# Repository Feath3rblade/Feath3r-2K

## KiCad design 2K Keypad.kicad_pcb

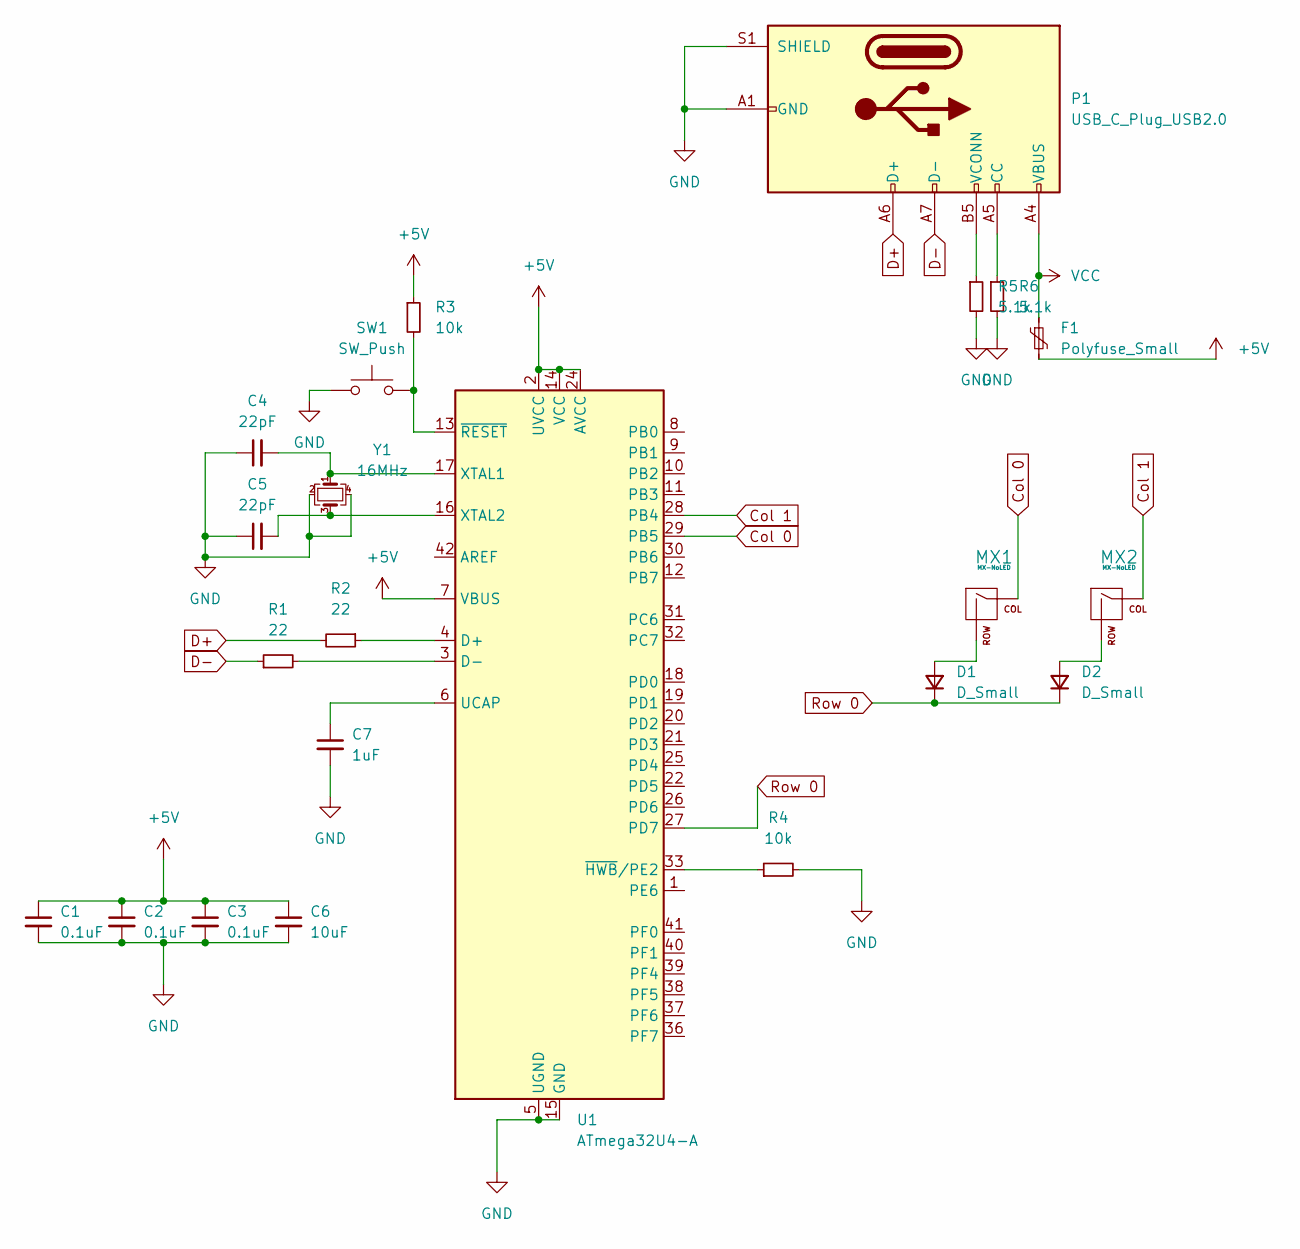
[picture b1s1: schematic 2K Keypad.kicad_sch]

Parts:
C1, C2, C3: 0.1uF; C_0805_2012Metric
C4, C5: 22pF; C_0805_2012Metric
C6: 10uF; C_0805_2012Metric
C7: 1uF; C_0805_2012Metric
D1, D2: D_Small; D_SOD-123
F1: Polyfuse_Small; Fuse_1206_3216Metric
MX1, MX2: MX-NoLED; MXOnly-1U-NoLED
P1: USB_C_Plug_USB2.0; USB_C_Receptacle_GCT_USB4085
R1, R2: 22; R_0805_2012Metric
R3, R4: 10k; R_0805_2012Metric
R5, R6: 5.1k; R_0805_2012Metric
SW1: SW_Push; SKQG-1155865
U1: ATmega32U4-A; TQFP-44_10x10mm_P0.8mm
Y1: 16MHz; Crystal_SMD_3225-4Pin_3.2x2.5mm

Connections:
+5V: C1.1, C2.1, C3.1, C6.1, F1.2, R3.1, U1.2 (UVCC), U1.7 (VBUS), U1.14 (VCC), U1.24 (AVCC), U1.34 (VCC), U1.44 (AVCC)
Col 0: MX1.1 (COL), U1.29 (PB5)
Col 1: MX2.1 (COL), U1.28 (PB4)
D+: P1.A6 (D+), R2.2
D-: P1.A7 (D-), R1.1
GND: C1.2, C2.2, C3.2, C4.1, C5.1, C6.2, C7.2, P1.A1 (GND), P1.A12 (GND), P1.B1 (GND), P1.B12 (GND), P1.S1 (SHIELD), R4.2, R5.2, R6.2, SW1.1, U1.5 (UGND), U1.15 (GND), U1.23 (GND), U1.35 (GND), U1.43 (GND), Y1.2, Y1.4
unnamed: C4.2, U1.17 (XTAL1), Y1.1
unnamed: C5.2, U1.16 (XTAL2), Y1.3
unnamed: C7.1, U1.6 (UCAP)
unnamed: D1.2 (A), MX1.2 (ROW)
unnamed: D2.2 (A), MX2.2 (ROW)
unnamed: R1.2, U1.3 (D-)
unnamed: R2.1, U1.4 (D+)
unnamed: R3.2, SW1.2, U1.13 (~RESET)
unnamed: R4.1, U1.33 (~HWB/PE2)
unnamed: P1.B5 (VCONN), R5.1
unnamed: P1.A5 (CC), R6.1
Row 0: D1.1 (K), D2.1 (K), U1.27 (PD7)
VCC: F1.1, P1.A4 (VBUS), P1.A9 (VBUS), P1.B4 (VBUS), P1.B9 (VBUS)

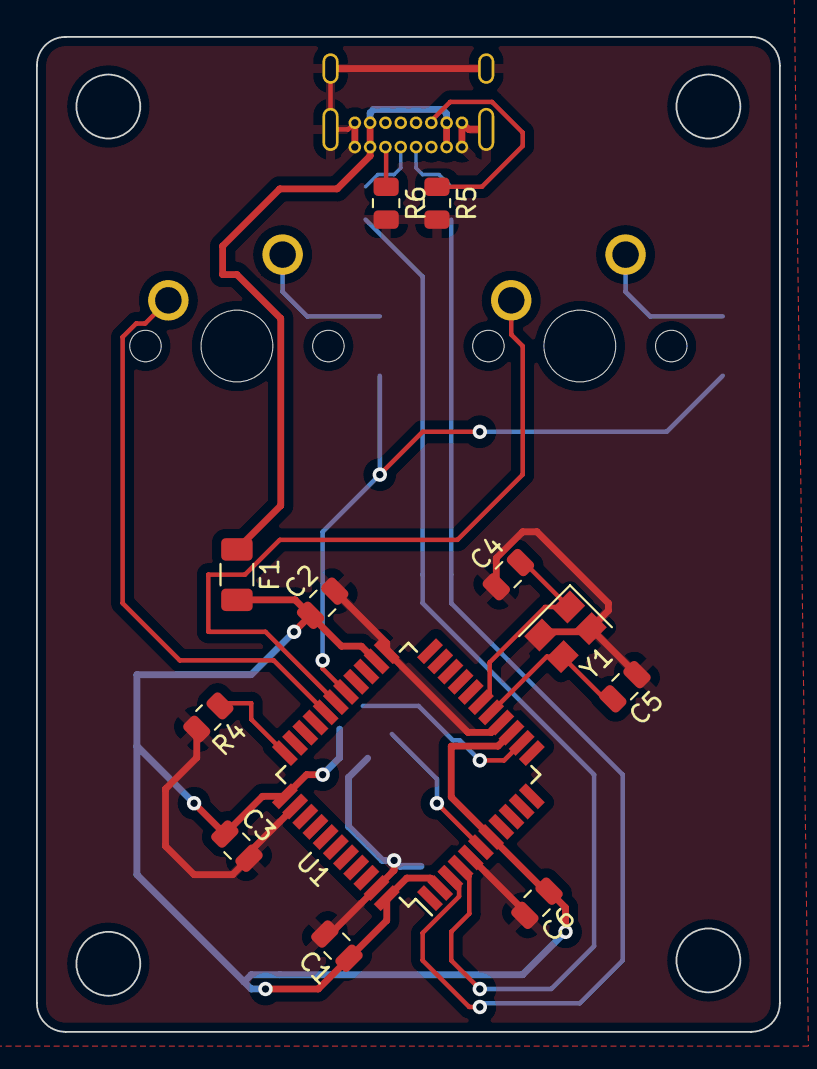
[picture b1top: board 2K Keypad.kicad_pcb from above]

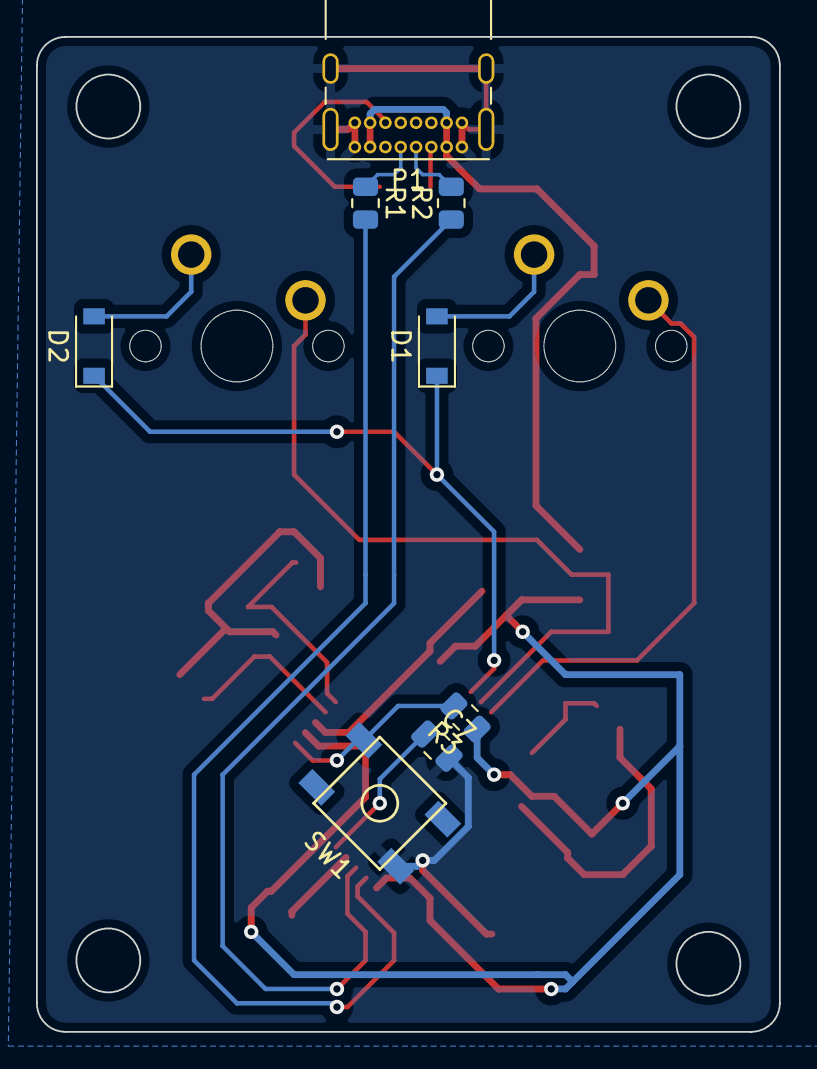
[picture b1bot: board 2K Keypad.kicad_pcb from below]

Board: 2 copper layers, 41.3 x 55.3 mm, 22 parts (8 on the bottom side), 19 nets.

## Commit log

2022-05-25 v1 of schematic and pcb
